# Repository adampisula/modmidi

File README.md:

# ModMIDI

ModMIDI is a modular MIDI hardware and software project. This repository brings the base board, pad shield, extension board, and shared Arduino library together in one monorepo.

> **Current state:** the KiCad source projects and PlatformIO configuration are present, but there is no board firmware or generated hardware PDF yet. Firmware and PDFs will be added/generated later; the current projects are not yet ready for a firmware build or hardware release.

## Repository map

| Path | Contents |
|---|---|
| [`boards/MM00/`](boards/MM00/README.md) | Base/controller board; KiCad source, PlatformIO configuration, and board instructions |
| [`boards/MM01/`](boards/MM01/README.md) | 4×4 pad shield; KiCad source, local footprint/model assets, PlatformIO configuration, and board instructions |
| [`boards/EX08/`](boards/EX08/README.md) | Passive 8-port extension board; KiCad source and board instructions, no firmware project |
| [`modmidi-arduino/`](modmidi-arduino/README.md) | Shared Arduino library used by the board firmware |

The `MIDIUSB` fork is maintained as a separate repository and is not nested in this monorepo. PlatformIO obtains it through the library dependency declaration; users do not need to clone the sibling repository separately.

## Prerequisites

- **KiCad 9.x** to open all hardware projects. MM00 uses KiCad 9-format files; MM01 and EX08 use KiCad 8-format files.
- **PlatformIO Core** for future firmware builds. Install PlatformIO yourself; this repository does not provide CI builds.
- Network access on the first PlatformIO dependency resolution to retrieve external libraries.

MM01's project includes its custom TL1105 footprint and the referenced STEP model using project-relative paths. A standard KiCad installation is still required for standard libraries and models. The included E-Switch asset did not come with license/provenance information; confirm its redistribution terms before publishing the repository publicly.

## Open the hardware

Open each KiCad project file:

- [MM00 base board](boards/MM00/hardware/MM00.kicad_pro)
- [MM01 4×4 pad shield](boards/MM01/hardware/MM01.kicad_pro)
- [EX08 extension board](boards/EX08/hardware/EX08.kicad_pro)

The editable KiCad projects are the hardware source of truth. PDFs, Gerbers, and BOMs are generated manually and are not produced by a script in this repository.

### Board PDFs

No PDFs are included yet. Adam will generate and add them manually under each board's `hardware/output/` directory. These links show the planned locations and will become available once the files are generated:

- MM00: [`boards/MM00/hardware/output/MM00-schematic.pdf`](boards/MM00/hardware/output/MM00-schematic.pdf) — pending
- MM01: [`boards/MM01/hardware/output/MM01-schematic.pdf`](boards/MM01/hardware/output/MM01-schematic.pdf) — pending
- EX08: [`boards/EX08/hardware/output/EX08-schematic.pdf`](boards/EX08/hardware/output/EX08-schematic.pdf) — pending

Gerbers and BOMs may also be added manually under the same `hardware/output/` directories. Intended output files are not ignored by the repository rules.

## Firmware

MM00 is the base board with the STM32F103C8 controller. MM01 is a shield driven by the MM00 controller; EX08 is passive and has no firmware. The per-board PlatformIO configurations select the STM32 Arduino target and link the local `modmidi-arduino/` library. USB support flags are included for USBLibrarySTM32/MIDIUSB.

For example, the MM00 configuration is in `boards/MM00/software/platformio.ini`:

```sh
cd boards/MM00/software
pio run
```

MM01 has a corresponding configuration under `boards/MM01/software/`. **These commands cannot build firmware yet:** neither software directory contains source files. Adam plans to add firmware later. No upload protocol is configured; confirm the actual programmer/bootloader and MM00's 16 MHz HSE clock/USB setup before attempting to flash. EX08 has no `software/` directory.

The board projects reference the library locally with `symlink://../../../modmidi-arduino`. Do not install the repository root as a PlatformIO library URL; the library's `library.json` is inside the `modmidi-arduino/` subdirectory. PlatformIO fetches the declared USB dependencies, including the `adampisula/MIDIUSB` branch `1.0.5` and `levi--g/USBLibrarySTM32` `~1.0.1`.

See the [`modmidi-arduino` README](modmidi-arduino/README.md) for API details and current implementation notes.

## Licensing

First-party ModMIDI code, documentation, and hardware are provided under the MIT License; see [`LICENSE`](LICENSE). Third-party dependencies and assets retain their own licenses and are not relicensed by the root MIT license. In particular, MIDIUSB is LGPL-2.1 and USBLibrarySTM32 is LGPL-3.0-or-later. Redistribution terms for the bundled E-Switch footprint/model still need confirmation before a public push.

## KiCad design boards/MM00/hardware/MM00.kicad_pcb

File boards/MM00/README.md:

# MM00 — ModMIDI Base

MM00 is the base/controller board for the ModMIDI modular system. It connects to the USB host, communicates with attached modules over I²C and an alert line, and breaks out MCU signals for compatible shields such as MM01.

**Revision:** 1.0, dated 2025-02-09 in the schematic title block.

## Hardware overview

- **MCU:** STM32F103C8, per the project specification. The schematic uses the `STM32F103C_8-B_Tx` family symbol.
- **Clocking:** Y1 is marked `16M 9p`; Y2 is marked `32K 12.5p`. The 16 MHz HSE is important when selecting/configuring the PlatformIO Arduino core; do not assume a Blue Pill's 8 MHz crystal.
- **USB:** USB D+/D−, USBLC6-4SC6 ESD protection, and an MCU-controlled D+ pull-up. USB-MIDI support is provided through the firmware dependencies.
- **Power:** a +5 V rail, LM66100 ideal-diode protection, AMS1117-3.3 regulation, and a separate 3.3 V analog rail (`3.3VA`). Check the schematic before applying power or connecting an external supply.
- **Module interface:** I²C SDA/SCL and the shared active-low alert net `NALERT`.
- **Indicators/debug:** status and error LED signals, UART TX/RX with an `EN_DEBUG` jumper, SWDIO/SWCLK programming signals, and a `BOOT_SELECT` jumper.

## Connectors and signal groups

| Reference | Connector | Signals / notes |
|---|---|---|
| J7 | 5-pin JST XH, in the POGO section | +5 V, GND, `I2C_SDA`, `I2C_SCL`, and `NALERT`. Use the schematic for the numbered pin order. |
| J8, J9 | Two 1×14, 2.54 mm headers | MCU GPIO and power breakout for compatible shields. The schematic labels include PA0–PA8, PB4, PB5, and PB8–PB15; use the schematic/PDF for the exact pin-to-header mapping and orientation. |
| USB connector | USB data and power interface | USB D+/D− with ESD protection and the controlled D+ pull-up. Confirm connector orientation and supply limits in the PCB/schematic before use. |
| Debug/programming headers and jumpers | UART, SWD, boot selection | Signals include UART TX/RX, SWDIO/SWCLK, `EN_DEBUG`, and `BOOT_SELECT`; follow the schematic for exact connector pin numbering. |

The table summarizes signal groups, not a substitute for the pin numbering and orientation shown in the KiCad design. Review the schematic before wiring a module or applying power.

## KiCad project and PDF

Open [`hardware/MM00.kicad_pro`](hardware/MM00.kicad_pro) in **KiCad 9.x**. MM00 uses the KiCad 9 file format; older KiCad versions may not open it correctly. The schematic symbols are embedded in the project.

- Schematic PDF: [`hardware/output/MM00-schematic.pdf`](hardware/output/MM00-schematic.pdf) — **not generated yet**; Adam will generate and add this file manually.
- The PDF, if present, is a reading copy; use the KiCad project as the editable source.

## Firmware build and flashing

The PlatformIO project is [`software/platformio.ini`](software/platformio.ini). It targets `genericSTM32F103C8`, uses Arduino, links the local `modmidi-arduino` library, and includes the USBLibrarySTM32 build flags required for USB-MIDI.

```sh
cd boards/MM00/software
pio run
```

There is currently **no firmware source** in `software/`, so `pio run` cannot produce firmware yet. Adam plans to add the firmware later. Once source is added, confirm the Arduino core's clock/USB setup for MM00's 16 MHz HSE and select the actual upload method before flashing. No upload protocol is currently configured; do not assume ST-Link or the UART bootloader without checking the hardware/programmer.

## BOM and manufacturing outputs

No BOM, Gerbers, or generated PDFs are currently included. Adam will generate hardware outputs manually under `hardware/output/`; intended PDF and flat BOM files are not ignored by the repository rules. Add manufacturing notes and links here when those files are available.

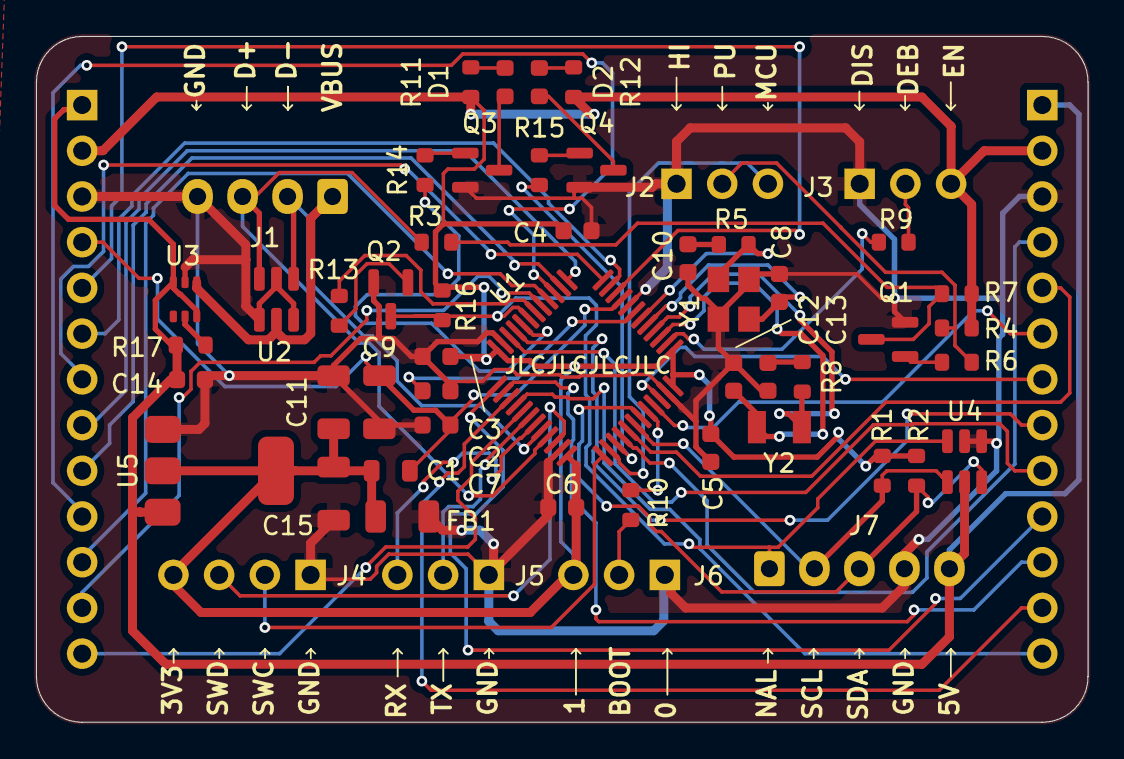
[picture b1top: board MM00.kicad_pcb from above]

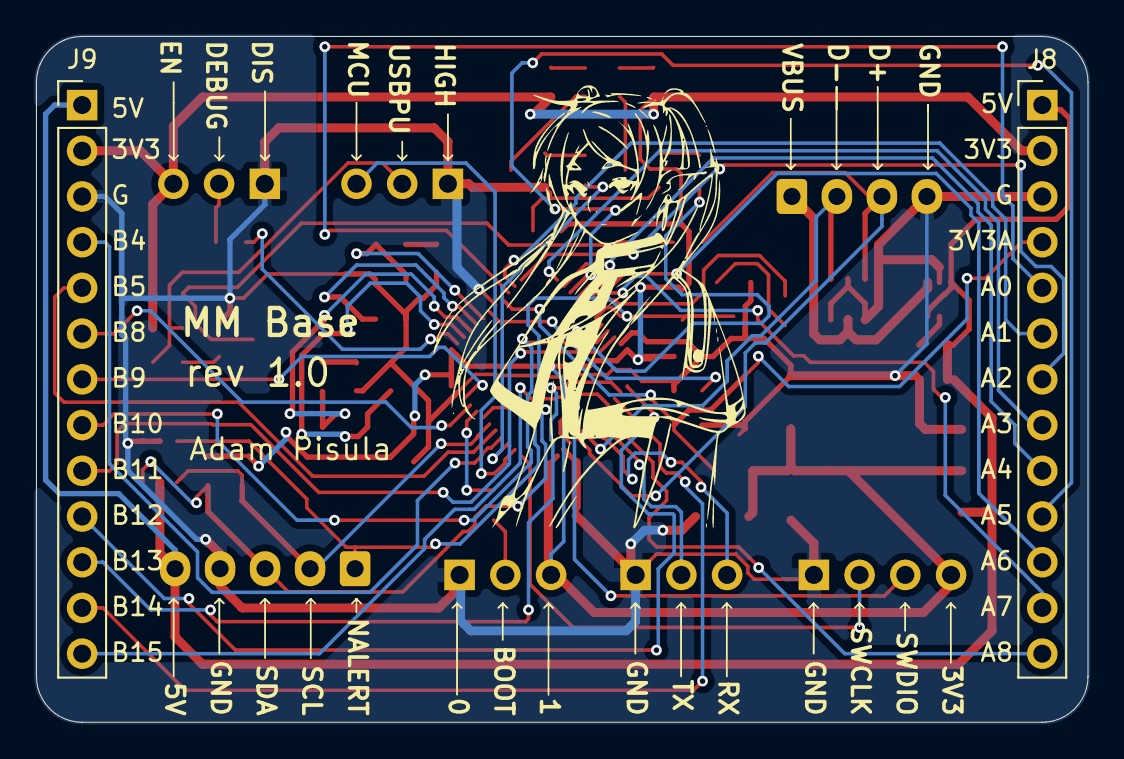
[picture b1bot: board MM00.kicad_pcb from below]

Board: 2 copper layers, 58.4 x 38.1 mm, 55 parts (2 on the bottom side), 59 nets.

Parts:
C1, C15: 10u; C_1206_3216Metric
C2, C3, C4, C5, C6, C14: 100n; C_0603_1608Metric
C7: 10n; C_0603_1608Metric
C8, C10: 10p; C_0603_1608Metric
C9, C11: 1u; C_1206_3216Metric
C12, C13: 15p; C_0603_1608Metric
D1: 2.6V 20mA (W); LED_0603_1608Metric
D2: 1.9V 20mA (R); LED_0603_1608Metric
FB1: 100R; L_0805_2012Metric
J1: 01x04; JST_XH_S4B-XH-A_1x04_P2.50mm_Horizontal
J2, J3, J5, J6: 01x03; PinHeader_1x03_P2.54mm_Horizontal
J4: 01x04; PinHeader_1x04_P2.54mm_Horizontal
J7: 01x05; JST_XH_S5B-XH-A_1x05_P2.50mm_Horizontal
J8, J9: 01x13; PinHeader_1x13_P2.54mm_Vertical
Q1, Q2, Q3, Q4: MMBT2222A; SOT-23
R1, R2, R10, R16: 10K; R_0603_1608Metric
R3: 1K5; R_0603_1608Metric
R4, R7, R9: 1K; R_0603_1608Metric
R5, R8: 0R; R_0603_1608Metric
R6, R13, R14, R15: 4.7K; R_0603_1608Metric
R11: 150R; R_0603_1608Metric
R12: 270R; R_0603_1608Metric
R17: 100K; R_0603_1608Metric
U1: STM32F103C_8-B_Tx; LQFP-48_7x7mm_P0.5mm
U2, U4: USBLC6-4SC6; SOT-23-6
U3: LM66100DCK; SOT-363_SC-70-6
U5: AMS1117-3.3; SOT-223-3_TabPin2
Y1: 16M 9p; Crystal_SMD_3225-4Pin_3.2x2.5mm
Y2: 32K 12.5p; Crystal_SMD_3215-2Pin_3.2x1.5mm

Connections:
+3.3V: C1.1, C2.1, C4.1, C5.1, C6.1, C11.1, C15.1, FB1.2, J3.3, J4.4, J6.3, J8.2, J9.2, R1.2, R2.2, R4.2, R7.2, R11.2, R12.2, R16.2, U1.1 (VBAT), U1.24 (VDD), U1.36 (VDD), U1.48 (VDD), U5.2 (VO)
+3.3VA: C7.1, C9.1, FB1.1, J8.4, U1.9 (VDDA)
+5V: C14.1, J7.5, J8.1, J9.1, R17.2, U3.3 (~CE), U3.6 (VOUT), U4.5 (VBUS), U5.3 (VI)
/ALERT_SELF: R13.1, U1.18 (PB0)
/BOOT_SELECT: R10.2, U1.44 (BOOT0)
/EN_DEBUG: R9.1, U1.2 (PC13)
/I2C_SCL: J7.2, R1.1, U1.42 (PB6), U4.4 (I/O3)
/I2C_SDA: J7.3, R2.1, U1.43 (PB7), U4.6 (I/O4)
/J_BOOT_S: J6.2, R10.1
/J_EN_DEBUG: J3.2, R9.2
/LED_ERROR: R15.2, U1.39 (PB3)
/LED_STATUS: R14.2, U1.20 (PB2)
/NALERT: J7.1, Q2.3 (C), R16.1, U1.19 (PB1), U4.3 (I/O2)
/NRST: C3.1, U1.7 (NRST)
/NUSB_PULLUP: J2.2, R4.1, R6.1
/NUSB_PULLUP_MCU: J2.3, U1.38 (PA15)
/OSC32_IN: C12.1, U1.3 (PC14), Y2.1
/OSC32_OUT: R8.2, U1.4 (PC15), Y2.2
/OSC_IN: C8.1, U1.5 (PD0), Y1.1
/OSC_OUT: R5.2, U1.6 (PD1), Y1.3
/PA0: J8.5, U1.10 (PA0)
/PA1: J8.6, U1.11 (PA1)
/PA2: J8.7, U1.12 (PA2)
/PA3: J8.8, U1.13 (PA3)
/PA4: J8.9, U1.14 (PA4)
/PA5: J8.10, U1.15 (PA5)
/PA6: J8.11, U1.16 (PA6)
/PA7: J8.12, U1.17 (PA7)
/PA8: J8.13, U1.29 (PA8)
/PB4: J9.4, U1.40 (PB4)
/PB5: J9.5, U1.41 (PB5)
/PB8: J9.6, U1.45 (PB8)
/PB9: J9.7, U1.46 (PB9)
/PB10: J9.8, U1.21 (PB10)
/PB11: J9.9, U1.22 (PB11)
/PB12: J9.10, U1.25 (PB12)
/PB13: J9.11, U1.26 (PB13)
/PB14: J9.12, U1.27 (PB14)
/PB15: J9.13, U1.28 (PB15)
/SWCLK: J4.2, U1.37 (PA14)
/SWDIO: J4.3, U1.34 (PA13)
/UART_RX: J5.3, U1.31 (PA10)
/UART_TX: J5.2, U1.30 (PA9)
/USB_DM: J1.2, U1.32 (PA11), U2.1 (I/O1)
/USB_DP: J1.3, R3.1, U1.33 (PA12), U2.3 (I/O2)
/USB_PULLUP: Q1.3 (C), R3.2, R7.1
/VBUS: J1.1, U2.5 (VBUS), U3.1 (VIN)
GND: C1.2, C2.2, C3.2, C4.2, C5.2, C6.2, C7.2, C8.2, C9.2, C10.2, C11.2, C12.2, C13.2, C14.2, C15.2, J1.4, J2.1, J3.1, J4.1, J5.1, J6.1, J7.4, J8.3, J9.3, Q1.2 (E), Q2.2 (E), Q3.2 (E), Q4.2 (E), U1.8 (VSSA), U1.23 (VSS), U1.35 (VSS), U1.47 (VSS), U2.2 (GND), U2.4 (I/O3), U2.6 (I/O4), U3.2 (GND), U4.1 (I/O1), U4.2 (GND), U5.1 (GND), Y1.2, Y1.4
unnamed: C10.1, R5.1
unnamed: C13.1, R8.1
unnamed: D1.2 (A), R11.1
unnamed: D1.1 (K), Q3.3 (C)
unnamed: D2.2 (A), R12.1
unnamed: D2.1 (K), Q4.3 (C)
unnamed: Q1.1 (B), R6.2
unnamed: Q2.1 (B), R13.2
unnamed: Q3.1 (B), R14.1
unnamed: Q4.1 (B), R15.1
unnamed: R17.1, U3.5 (ST)

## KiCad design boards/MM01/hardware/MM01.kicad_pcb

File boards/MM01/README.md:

# MM01 — ModMIDI 4×4 Pad Shield

MM01 is a 4×4 button and LED shield for the ModMIDI system. It does **not** contain its own MCU; its signals connect through MM00, whose STM32F103C8 runs any future MM01 firmware.

**Revision:** 1, dated 2025-02-09 in the schematic title block.

## Hardware overview

- Sixteen TL1105 push buttons are scanned through two 74HC165 parallel-in/serial-out shift registers.
- 74HC14 Schmitt-trigger logic conditions/debounces the button signals.
- WS2813 addressable RGB LEDs form the LED array.
- An AO3400A MOSFET provides the LED-data level-shifting stage between the controller logic and LED signal path.
- The shield uses +5 V from the base-board headers for the LED circuitry; it has no standalone MCU or firmware target.

## Connectors and controller signals

| Reference | Connector | Signals / notes |
|---|---|---|
| J1, J2 | Two 1×13, 2.54 mm sockets | Shield connections to the matching MM00 base-board headers. Check the schematic for pin numbering and orientation. |
| MM00 GPIO | Controller signals on the shield interface | The schematic maps the key signals as shown below. |

| MM00 MCU pin | MM01 signal | Function |
|---|---|---|
| PA2 | `LED_IN_MCU` | LED data input to the shield's level-shifting/LED path |
| PA3 | `NBUTTON_LOAD` | Loads the button shift-register state |
| PA5 | `SERIAL_CLOCK` | Shift-register serial clock |
| PA6 | `SERIAL_OUT` | Button shift-register serial data back to the MCU |

The shield takes its +5 V supply through the base-board connection. Use the schematic for the complete connector pin order, power pins, and electrical details before connecting a board.

## KiCad project, libraries, and PDF

Open [`hardware/MM01.kicad_pro`](hardware/MM01.kicad_pro) in **KiCad 9.x**. MM01 uses KiCad 8-format files; KiCad 9.x is the common version recommended for all ModMIDI boards.

The project includes a local footprint table at [`hardware/fp-lib-table`](hardware/fp-lib-table), the used `SW-Eswitch:TL1105` footprint under `hardware/footprints/SW-Eswitch.pretty/`, and the referenced STEP model under `hardware/3dmodels/SW-Eswitch.3dshapes/`. The PCB stores the placed 2D footprint geometry and uses project-relative `${KIPRJMOD}` paths for the bundled asset. A standard KiCad installation is still required for the standard libraries and models. The bundled E-Switch asset had no accompanying license/provenance document in the source library; its redistribution terms must be confirmed before public publication.

- Schematic PDF: [`hardware/output/MM01-schematic.pdf`](hardware/output/MM01-schematic.pdf) — **not generated yet**; Adam will generate and add it manually.

## Firmware build and flashing

The PlatformIO project is [`software/platformio.ini`](software/platformio.ini). It targets the MM00 STM32F103C8 controller with Arduino, links the local `modmidi-arduino` library, and enables the USBLibrarySTM32 flags.

```sh
cd boards/MM01/software
pio run
```

There is currently **no firmware source** in `software/`, so this project cannot produce firmware yet. Adam plans to add the firmware later. When firmware is added, verify the pin mapping against the schematic and build/flash the **MM00 controller**; MM01 itself is a shield and cannot be flashed. The upload protocol remains unset until the actual programmer/bootloader is confirmed.

## BOM and manufacturing outputs

No BOM, Gerbers, or generated PDFs are currently included. Adam will generate hardware outputs manually under `hardware/output/`; intended PDF and flat BOM files are not ignored by the repository rules. Add manufacturing notes and links here when those files are available.

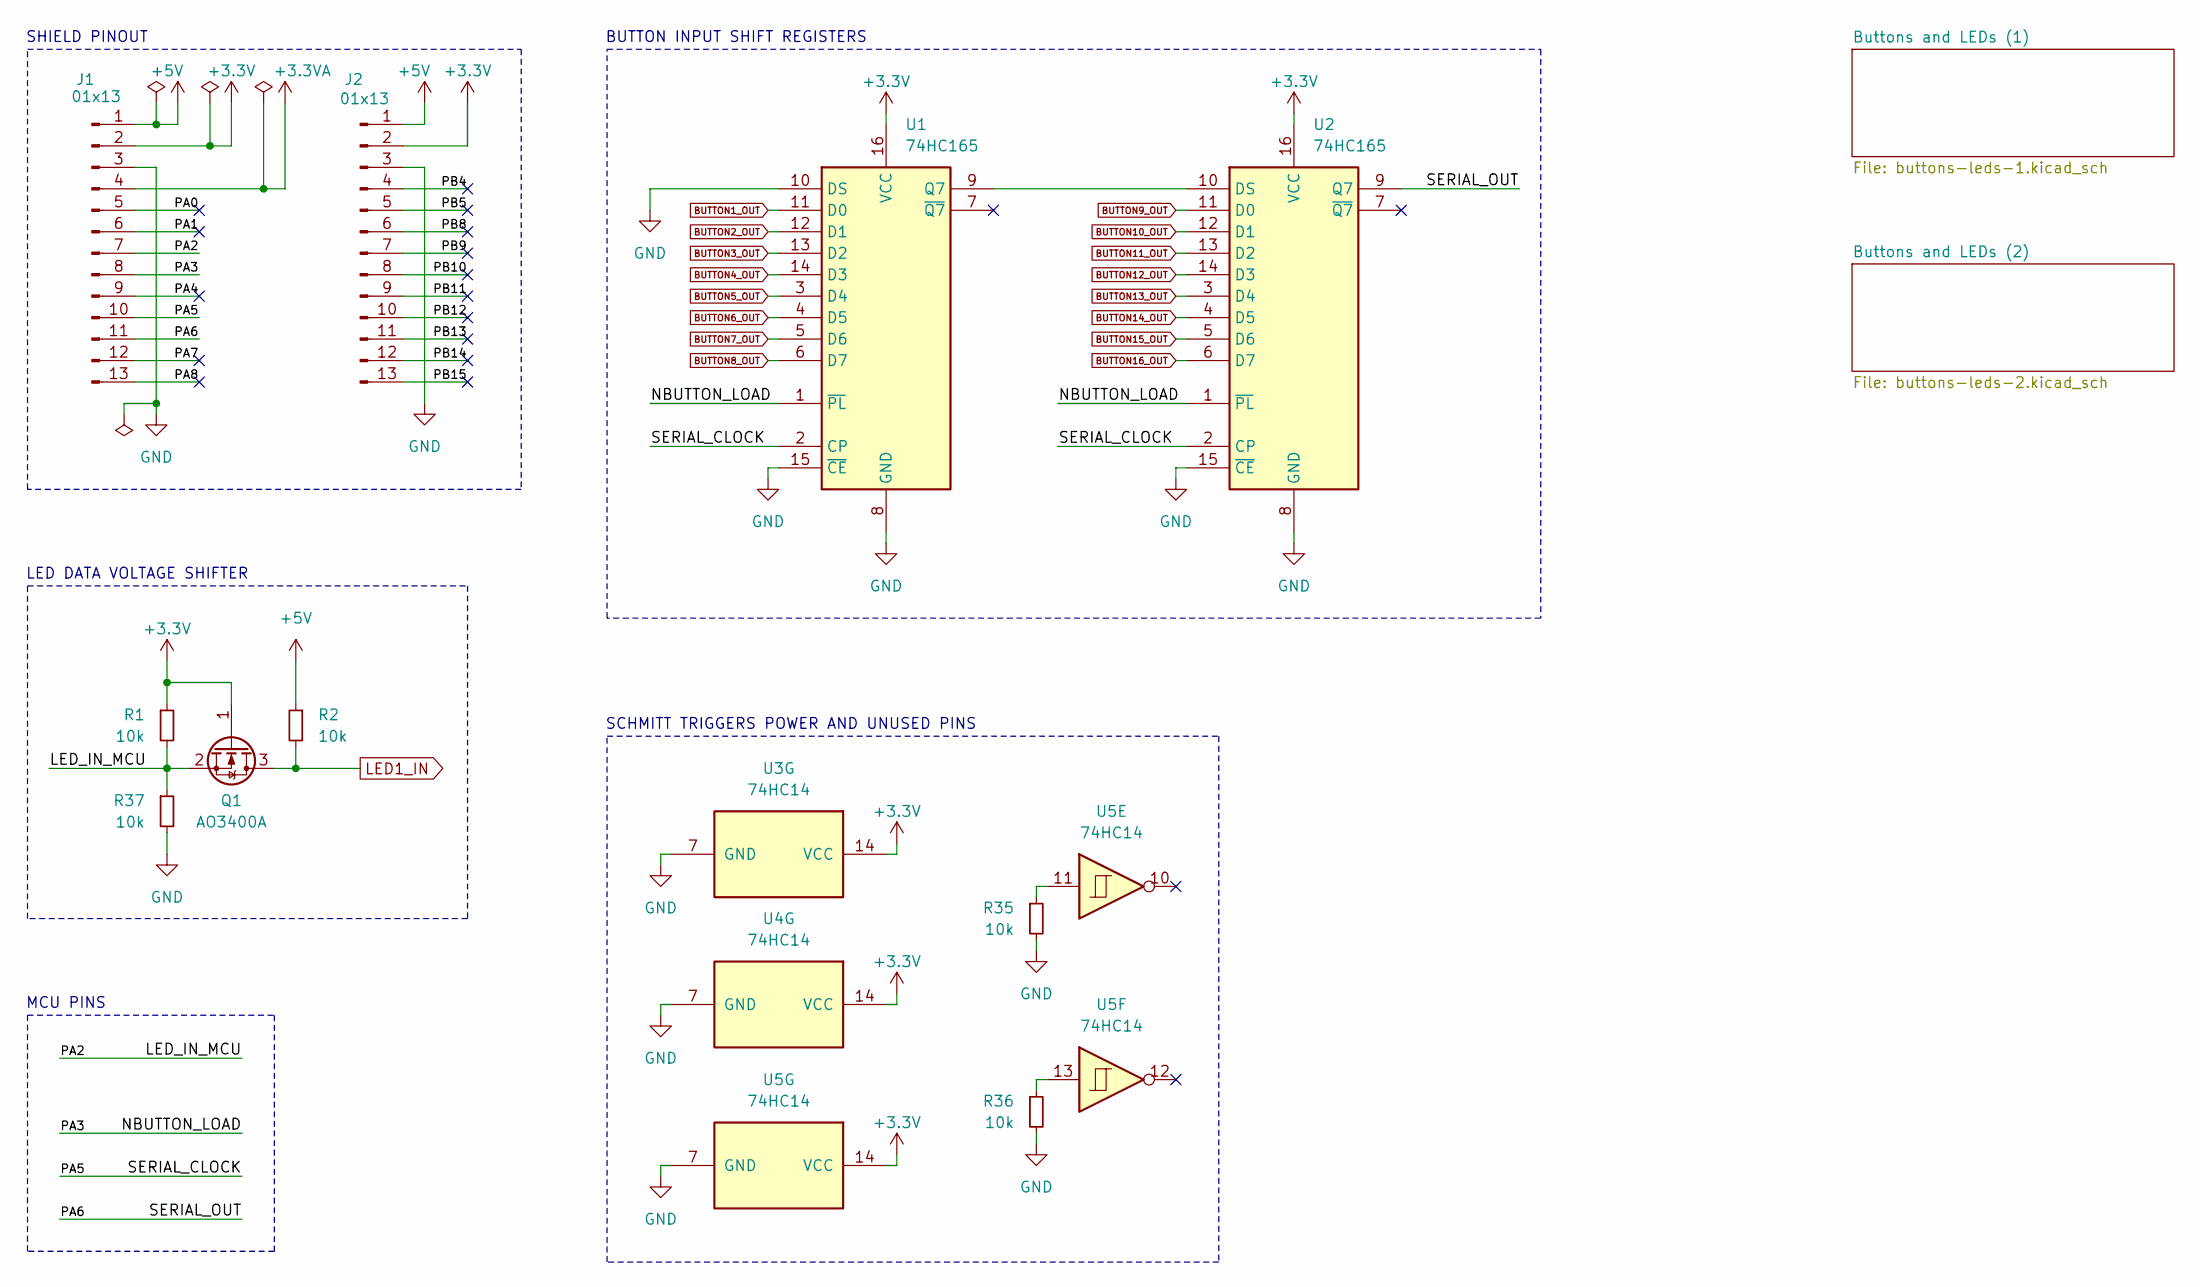
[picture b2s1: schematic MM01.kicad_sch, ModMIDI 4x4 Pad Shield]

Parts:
J1, J2: 01x13; PinSocket_1x13_P2.54mm_Vertical
Q1: AO3400A; SOT-23
R1, R2, R35, R36, R37: 10k; R_0603_1608Metric
U1, U2: 74HC165; SOIC-16_3.9x9.9mm_P1.27mm
U3, U4, U5: 74HC14; DIP-14_W7.62mm_SMDSocket_SmallPads

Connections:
+3.3V: J1.2, J2.2, Q1.1 (G), R1.1, U1.16 (VCC), U2.16 (VCC), U3.14 (VCC), U4.14 (VCC), U5.14 (VCC); also elsewhere on the board
+3.3VA: J1.4
+5V: J1.1, J2.1, R2.1; also elsewhere on the board
/LED_IN_MCU: J1.7, Q1.2 (S), R1.2, R37.1
/NBUTTON_LOAD: J1.8, U1.1 (~PL), U2.1 (~PL)
/PA0: J1.5
/PA1: J1.6
/PA4: J1.9
/PA5: J1.10, U1.2 (CP), U2.2 (CP)
/PA6: J1.11, U2.9 (Q7)
/PA7: J1.12
/PA8: J1.13
/PB4: J2.4
/PB5: J2.5
/PB8: J2.6
/PB9: J2.7
/PB10: J2.8
/PB11: J2.9
/PB12: J2.10
/PB13: J2.11
/PB14: J2.12
/PB15: J2.13
BUTTON1_OUT: U1.11 (D0); also elsewhere on the board
BUTTON2_OUT: U1.12 (D1); also elsewhere on the board
BUTTON3_OUT: U1.13 (D2); also elsewhere on the board
BUTTON4_OUT: U1.14 (D3); also elsewhere on the board
BUTTON5_OUT: U1.3 (D4); also elsewhere on the board
BUTTON6_OUT: U1.4 (D5); also elsewhere on the board
BUTTON7_OUT: U1.5 (D6); also elsewhere on the board
BUTTON8_OUT: U1.6 (D7); also elsewhere on the board
BUTTON9_OUT: U2.11 (D0); also elsewhere on the board
BUTTON10_OUT: U2.12 (D1); also elsewhere on the board
BUTTON11_OUT: U2.13 (D2); also elsewhere on the board
BUTTON12_OUT: U2.14 (D3); also elsewhere on the board
BUTTON13_OUT: U2.3 (D4); also elsewhere on the board
BUTTON14_OUT: U2.4 (D5); also elsewhere on the board
BUTTON15_OUT: U2.5 (D6); also elsewhere on the board
BUTTON16_OUT: U2.6 (D7); also elsewhere on the board
GND: J1.3, J2.3, R35.2, R36.2, R37.2, U1.8 (GND), U1.10 (DS), U1.15 (~CE), U2.8 (GND), U2.15 (~CE), U3.7 (GND), U4.7 (GND), U5.7 (GND); also elsewhere on the board
LED1_IN: Q1.3 (D), R2.2; also elsewhere on the board
unnamed: R35.1, U5.11
unnamed: R36.1, U5.13
unnamed: U1.9 (Q7), U2.10 (DS)

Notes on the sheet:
BUTTON INPUT SHIFT REGISTERS
SCHMITT TRIGGERS POWER AND UNUSED PINS
MCU PINS
SHIELD PINOUT
LED DATA VOLTAGE SHIFTER

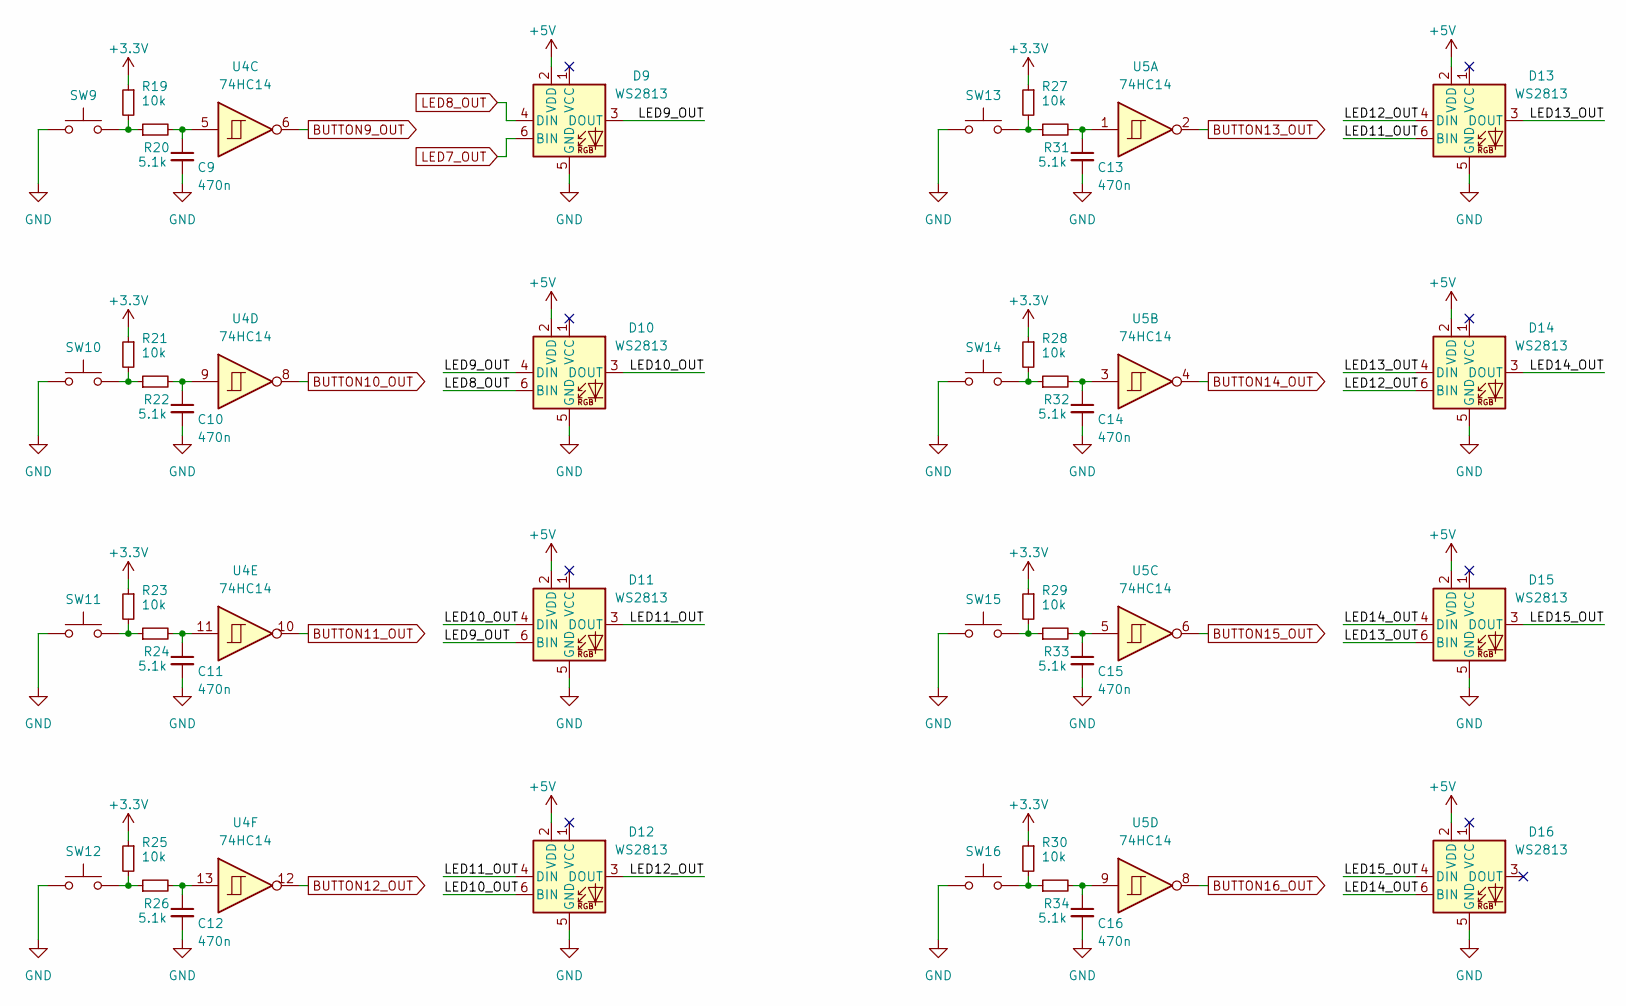
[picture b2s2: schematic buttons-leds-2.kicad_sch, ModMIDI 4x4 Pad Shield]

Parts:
C9, C10, C11, C12, C13, C14, C15, C16: 470n; C_0603_1608Metric
D9, D10, D11, D12, D13, D14, D15, D16: WS2813; LED_WS2812_PLCC6_5.0x5.0mm_P1.6mm
R19, R21, R23, R25, R27, R28, R29, R30: 10k; R_0603_1608Metric
R20, R22, R24, R26, R31, R32, R33, R34: 5.1k; R_0603_1608Metric
SW9, SW10, SW11, SW12, SW13, SW14, SW15, SW16: SW_Push; TL1105
U4, U5: 74HC14; DIP-14_W7.62mm_SMDSocket_SmallPads

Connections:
+3.3V: R19.1, R21.1, R23.1, R25.1, R27.1, R28.1, R29.1, R30.1; also elsewhere on the board
+5V: D9.2 (VDD), D10.2 (VDD), D11.2 (VDD), D12.2 (VDD), D13.2 (VDD), D14.2 (VDD), D15.2 (VDD), D16.2 (VDD); also elsewhere on the board
/Buttons and LEDs (2)/LED9_OUT: D9.3 (DOUT), D10.4 (DIN), D11.6 (BIN)
/Buttons and LEDs (2)/LED10_OUT: D10.3 (DOUT), D11.4 (DIN), D12.6 (BIN)
/Buttons and LEDs (2)/LED11_OUT: D11.3 (DOUT), D12.4 (DIN), D13.6 (BIN)
/Buttons and LEDs (2)/LED12_OUT: D12.3 (DOUT), D13.4 (DIN), D14.6 (BIN)
/Buttons and LEDs (2)/LED13_OUT: D13.3 (DOUT), D14.4 (DIN), D15.6 (BIN)
/Buttons and LEDs (2)/LED14_OUT: D14.3 (DOUT), D15.4 (DIN), D16.6 (BIN)
/Buttons and LEDs (2)/LED15_OUT: D15.3 (DOUT), D16.4 (DIN)
BUTTON9_OUT: U4.6; also elsewhere on the board
BUTTON10_OUT: U4.8; also elsewhere on the board
BUTTON11_OUT: U4.10; also elsewhere on the board
BUTTON12_OUT: U4.12; also elsewhere on the board
BUTTON13_OUT: U5.2; also elsewhere on the board
BUTTON14_OUT: U5.4; also elsewhere on the board
BUTTON15_OUT: U5.6; also elsewhere on the board
BUTTON16_OUT: U5.8; also elsewhere on the board
GND: C9.2, C10.2, C11.2, C12.2, C13.2, C14.2, C15.2, C16.2, D9.5 (GND), D10.5 (GND), D11.5 (GND), D12.5 (GND), D13.5 (GND), D14.5 (GND), D15.5 (GND), D16.5 (GND), SW9.1, SW10.1, SW11.1, SW12.1, SW13.1, SW14.1, SW15.1, SW16.1; also elsewhere on the board
LED7_OUT: D9.6 (BIN); also elsewhere on the board
LED8_OUT: D9.4 (DIN), D10.6 (BIN); also elsewhere on the board
unnamed: C9.1, R20.2, U4.5
unnamed: C10.1, R22.2, U4.9
unnamed: C11.1, R24.2, U4.11
unnamed: C12.1, R26.2, U4.13
unnamed: C13.1, R31.2, U5.1
unnamed: C14.1, R32.2, U5.3
unnamed: C15.1, R33.2, U5.5
unnamed: C16.1, R34.2, U5.9
unnamed: R19.2, R20.1, SW9.2
unnamed: R21.2, R22.1, SW10.2
unnamed: R23.2, R24.1, SW11.2
unnamed: R25.2, R26.1, SW12.2
unnamed: R27.2, R31.1, SW13.2
unnamed: R28.2, R32.1, SW14.2
unnamed: R29.2, R33.1, SW15.2
unnamed: R30.2, R34.1, SW16.2

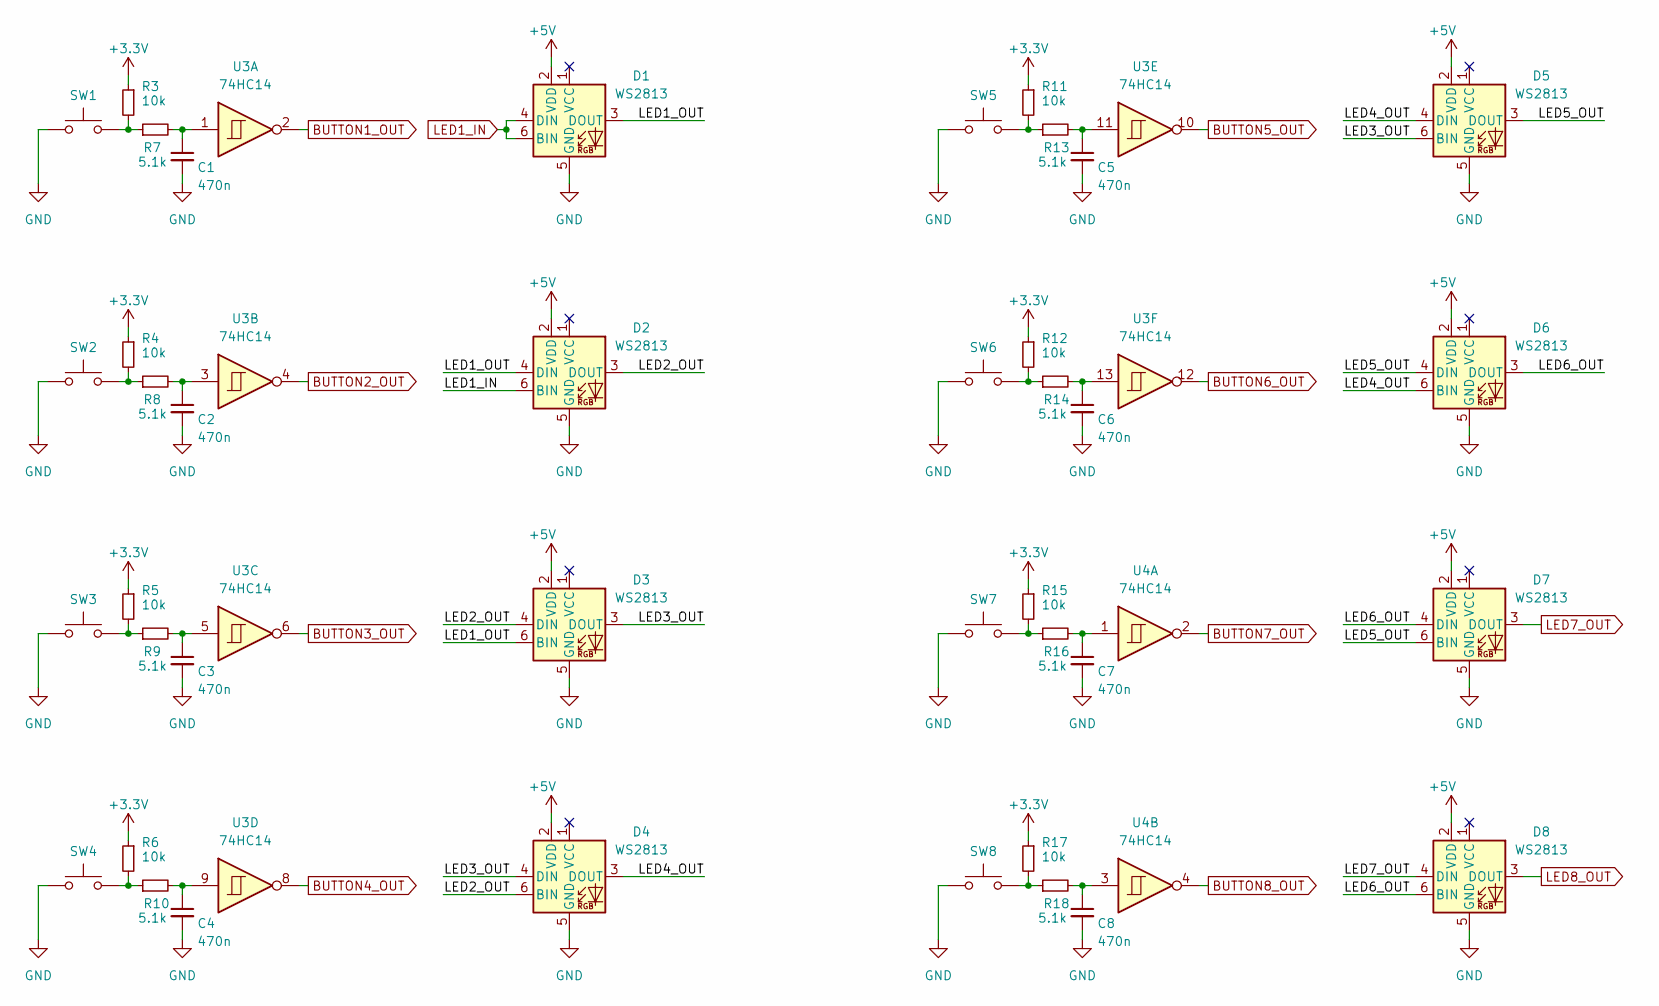
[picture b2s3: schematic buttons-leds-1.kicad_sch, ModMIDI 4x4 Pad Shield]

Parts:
C1, C2, C3, C4, C5, C6, C7, C8: 470n; C_0603_1608Metric
D1, D2, D3, D4, D5, D6, D7, D8: WS2813; LED_WS2812_PLCC6_5.0x5.0mm_P1.6mm
R3, R4, R5, R6, R11, R12, R15, R17: 10k; R_0603_1608Metric
R7, R8, R9, R10, R13, R14, R16, R18: 5.1k; R_0603_1608Metric
SW1, SW2, SW3, SW4, SW5, SW6, SW7, SW8: SW_Push; TL1105
U3, U4: 74HC14; DIP-14_W7.62mm_SMDSocket_SmallPads

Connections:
+3.3V: R3.1, R4.1, R5.1, R6.1, R11.1, R12.1, R15.1, R17.1; also elsewhere on the board
+5V: D1.2 (VDD), D2.2 (VDD), D3.2 (VDD), D4.2 (VDD), D5.2 (VDD), D6.2 (VDD), D7.2 (VDD), D8.2 (VDD); also elsewhere on the board
/Buttons and LEDs (1)/LED1_OUT: D1.3 (DOUT), D2.4 (DIN), D3.6 (BIN)
/Buttons and LEDs (1)/LED2_OUT: D2.3 (DOUT), D3.4 (DIN), D4.6 (BIN)
/Buttons and LEDs (1)/LED3_OUT: D3.3 (DOUT), D4.4 (DIN), D5.6 (BIN)
/Buttons and LEDs (1)/LED4_OUT: D4.3 (DOUT), D5.4 (DIN), D6.6 (BIN)
/Buttons and LEDs (1)/LED5_OUT: D5.3 (DOUT), D6.4 (DIN), D7.6 (BIN)
/Buttons and LEDs (1)/LED6_OUT: D6.3 (DOUT), D7.4 (DIN), D8.6 (BIN)
BUTTON1_OUT: U3.2; also elsewhere on the board
BUTTON2_OUT: U3.4; also elsewhere on the board
BUTTON3_OUT: U3.6; also elsewhere on the board
BUTTON4_OUT: U3.8; also elsewhere on the board
BUTTON5_OUT: U3.10; also elsewhere on the board
BUTTON6_OUT: U3.12; also elsewhere on the board
BUTTON7_OUT: U4.2; also elsewhere on the board
BUTTON8_OUT: U4.4; also elsewhere on the board
GND: C1.2, C2.2, C3.2, C4.2, C5.2, C6.2, C7.2, C8.2, D1.5 (GND), D2.5 (GND), D3.5 (GND), D4.5 (GND), D5.5 (GND), D6.5 (GND), D7.5 (GND), D8.5 (GND), SW1.1, SW2.1, SW3.1, SW4.1, SW5.1, SW6.1, SW7.1, SW8.1; also elsewhere on the board
LED1_IN: D1.4 (DIN), D1.6 (BIN), D2.6 (BIN); also elsewhere on the board
LED7_OUT: D7.3 (DOUT), D8.4 (DIN); also elsewhere on the board
LED8_OUT: D8.3 (DOUT); also elsewhere on the board
unnamed: C1.1, R7.2, U3.1
unnamed: C2.1, R8.2, U3.3
unnamed: C3.1, R9.2, U3.5
unnamed: C4.1, R10.2, U3.9
unnamed: C5.1, R13.2, U3.11
unnamed: C6.1, R14.2, U3.13
unnamed: C7.1, R16.2, U4.1
unnamed: C8.1, R18.2, U4.3
unnamed: R3.2, R7.1, SW1.2
unnamed: R4.2, R8.1, SW2.2
unnamed: R5.2, R9.1, SW3.2
unnamed: R6.2, R10.1, SW4.2
unnamed: R11.2, R13.1, SW5.2
unnamed: R12.2, R14.1, SW6.2
unnamed: R15.2, R16.1, SW7.2
unnamed: R17.2, R18.1, SW8.2

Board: 2 copper layers, 93 parts (0 on the bottom side), 74 nets, no tracks yet.

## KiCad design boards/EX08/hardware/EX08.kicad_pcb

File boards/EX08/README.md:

# EX08 — ModMIDI Extension Board (8 ports)

EX08 is a passive wiring/extension board for connecting ModMIDI modules. It contains no MCU, so it has no PlatformIO project, firmware, or flashing procedure.

**Revision:** 1, dated 2025-02-15 in the schematic title block.

## Connectors and signals

The schematic shows four 5-pin input/output connectors and eight 5-pin pogo connectors. Each carries the shared ModMIDI module signals:

| References | Role | Signals |
|---|---|---|
| J_IN1, J_IN2 | Input connectors | `5V`, GND, `I2C_SDA`, `I2C_SCL`, `NALERT` |
| J_OUT1, J_OUT2 | Output connectors | `5V`, GND, `I2C_SDA`, `I2C_SCL`, `NALERT` |
| J_POGO_M1–M4, J_POGO_F1–F4 | Male/female pogo connections | `5V`, GND, `I2C_SDA`, `I2C_SCL`, `NALERT` |

This is a passive interconnect board; observe the schematic's connector pin numbering, orientation, and power distribution when wiring it. Do not treat the signal list as a pin-order table.

## KiCad project and PDF

Open [`hardware/EX08.kicad_pro`](hardware/EX08.kicad_pro) in **KiCad 9.x**. EX08 uses KiCad 8-format files; KiCad 9.x is the common version recommended for all ModMIDI boards.

- Schematic PDF: [`hardware/output/EX08-schematic.pdf`](hardware/output/EX08-schematic.pdf) — **not generated yet**; Adam will generate and add this file manually.
- The KiCad project is the editable source; the PDF will be a reading copy.

## BOM and manufacturing outputs

No BOM, Gerbers, or generated PDFs are currently included. Adam will generate hardware outputs manually under `hardware/output/`; intended PDF and flat BOM files are not ignored by the repository rules. Add manufacturing notes and links here when those files are available.

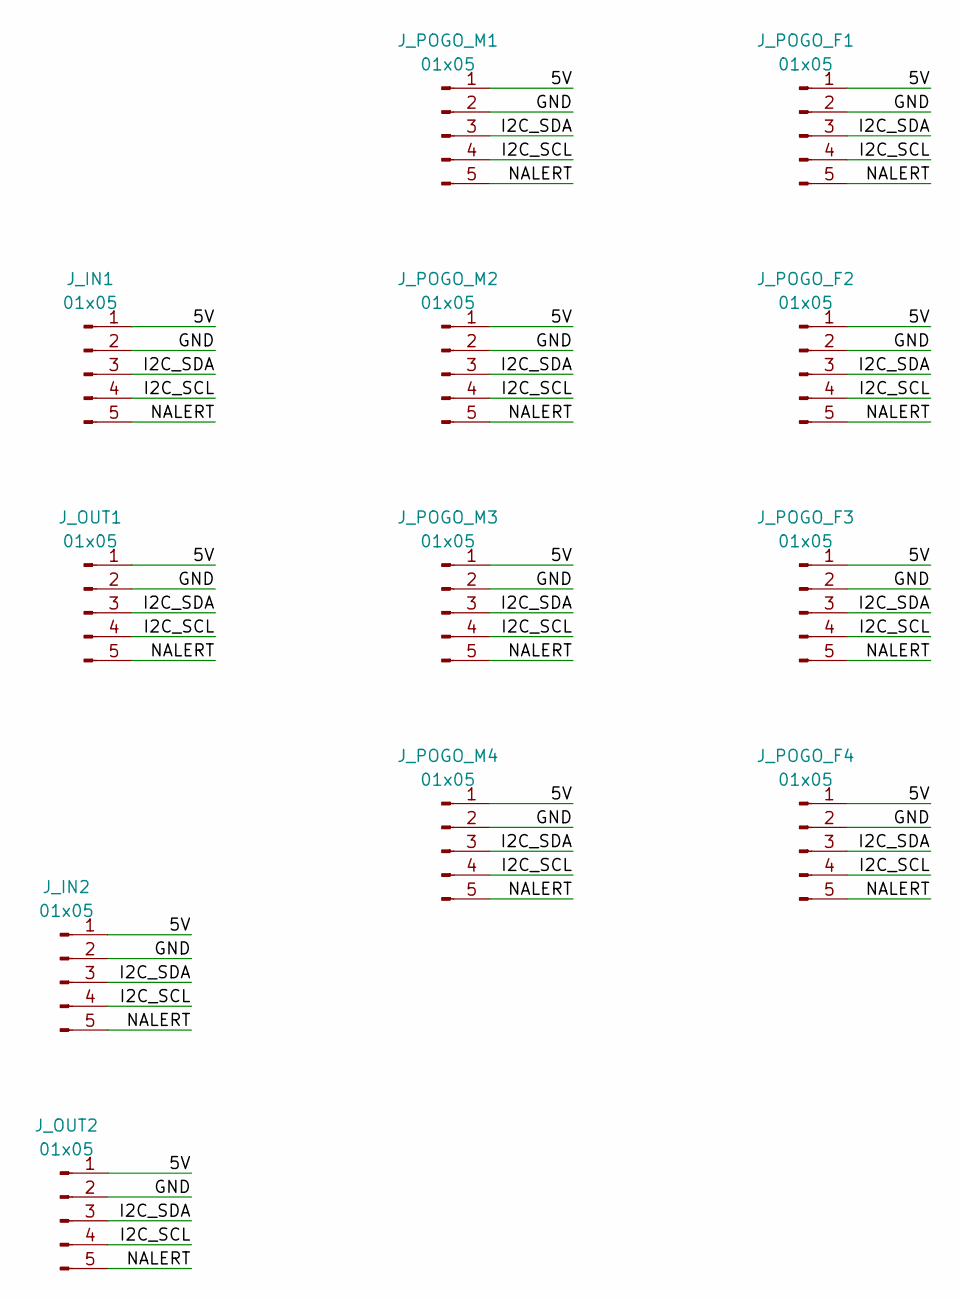
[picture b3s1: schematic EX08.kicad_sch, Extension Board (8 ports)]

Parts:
J_IN1: 01x05; JST_XH_S5B-XH-A_1x05_P2.50mm_Horizontal
J_IN2: 01x05; PinHeader_1x05_P2.54mm_Vertical
J_OUT1: 01x05; PinHeader_1x05_P2.54mm_Horizontal
J_OUT2: 01x05; PinSocket_1x05_P2.54mm_Vertical
J_POGO_F1, J_POGO_F2, J_POGO_F3, J_POGO_F4: 01x05; JST_XH_S5B-XH-A_1x05_P2.50mm_Horizontal
J_POGO_M1, J_POGO_M2, J_POGO_M3, J_POGO_M4: 01x05; JST_XH_S5B-XH-A_1x05_P2.50mm_Horizontal

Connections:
/5V: J_IN1.1, J_IN2.1, J_OUT1.1, J_OUT2.1, J_POGO_F1.1, J_POGO_F2.1, J_POGO_F3.1, J_POGO_F4.1, J_POGO_M1.1, J_POGO_M2.1, J_POGO_M3.1, J_POGO_M4.1
/GND: J_IN1.2, J_IN2.2, J_OUT1.2, J_OUT2.2, J_POGO_F1.2, J_POGO_F2.2, J_POGO_F3.2, J_POGO_F4.2, J_POGO_M1.2, J_POGO_M2.2, J_POGO_M3.2, J_POGO_M4.2
/I2C_SCL: J_IN1.4, J_IN2.4, J_OUT1.4, J_OUT2.4, J_POGO_F1.4, J_POGO_F2.4, J_POGO_F3.4, J_POGO_F4.4, J_POGO_M1.4, J_POGO_M2.4, J_POGO_M3.4, J_POGO_M4.4
/I2C_SDA: J_IN1.3, J_IN2.3, J_OUT1.3, J_OUT2.3, J_POGO_F1.3, J_POGO_F2.3, J_POGO_F3.3, J_POGO_F4.3, J_POGO_M1.3, J_POGO_M2.3, J_POGO_M3.3, J_POGO_M4.3
/NALERT: J_IN1.5, J_IN2.5, J_OUT1.5, J_OUT2.5, J_POGO_F1.5, J_POGO_F2.5, J_POGO_F3.5, J_POGO_F4.5, J_POGO_M1.5, J_POGO_M2.5, J_POGO_M3.5, J_POGO_M4.5

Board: 2 copper layers, 12 parts (5 on the bottom side), 5 nets, no tracks yet.
